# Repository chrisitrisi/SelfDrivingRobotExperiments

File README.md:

# SelfDrivingRobotExperiments

Wir verwenden ein vorgegebenes Modellfahrzeug als Basis. Wir entwickeln dafür eine eigene Platine, programmieren die Fahrzeugsoftware neu und erstellen ein eigenes 3D-Modell. Zusätzliche Entfernungssensoren sind eine Option.

| Bereich | Arbeitsstand |
| --- | --- |
| Hardware (Christopher) | [PCB](https://github.com/chrisitrisi/SelfDrivingRobotExperiments/tree/PCB/PCB) enthält KiCad-Projekte, darunter den Liniensensor. |
| Software | [Main_code](https://github.com/chrisitrisi/SelfDrivingRobotExperiments/tree/Main_code), [code](https://github.com/chrisitrisi/SelfDrivingRobotExperiments/tree/code) und [Test](https://github.com/chrisitrisi/SelfDrivingRobotExperiments/tree/Test) enthalten ESP-IDF-Sensorversuche. Den Ausgangsbranch pro Aufgabe im Issue angeben. |
| 3D-Design | [3D_Design](https://github.com/chrisitrisi/SelfDrivingRobotExperiments/tree/3D_Design/3D_Design-Modelling) enthält Fahrzeug- und Gehäusemodelle sowie Exporte. |
| Diplomarbeitsunterlagen | [Dokumentation](https://github.com/chrisitrisi/SelfDrivingRobotExperiments/tree/Dokumentation/Dokumentation) |

## Gemeinsam arbeiten

1. Erstellt ein [Issue](https://github.com/chrisitrisi/SelfDrivingRobotExperiments/issues/new) mit Ziel, Rolle, Ausgangsbranch und einem überprüfbaren Ergebnis. Bei Aufgaben für mehrere Bereiche beschreibt ihr die Teilaufgaben im selben Issue.
2. Lest die aktuelle [AGENTS.md](https://github.com/chrisitrisi/SelfDrivingRobotExperiments/blob/master/AGENTS.md), die [Schnittstellen](https://github.com/chrisitrisi/SelfDrivingRobotExperiments/blob/master/docs/schnittstellen.md) und die neuesten Issue-Kommentare. Die zentralen Dateien liegen auf `master`, auch wenn ihr gerade einen anderen Branch bearbeitet.
3. Erstellt euren Aufgabenbranch vom vereinbarten Fachbranch. Öffnet den Pull Request zurück in diesen Fachbranch und verlinkt das Issue. Änderungen an gemeinsamen Regeln und Schnittstellen gehen in einen eigenen Pull Request gegen `master`.
4. Haltet im Issue fest, was geprüft wurde, was offen ist und von welcher Rolle ihr eine Antwort braucht.

### KI-Fragen zwischen den Rollen

Die KIs der Rollen klären Fragen untereinander über Issues, ohne dass die Menschen dazwischen müssen: Eine KI stellt eine **KI-Frage** an eine Rolle (Labels `ki-frage` + `an:hardware`, `an:software` oder `an:3d`), die KI der Zielrolle antwortet im selben Issue. Fragen an die Hardware beantwortet eine GitHub Action mit Claude sofort automatisch (Rückfragen mit `@hw-ki`). Menschen werden nur über das Label [`braucht-mensch`](https://github.com/chrisitrisi/SelfDrivingRobotExperiments/issues?q=is%3Aopen+label%3Abraucht-mensch) gebraucht.

- Ablauf, Befehle, Antwortformat: [docs/ki-austausch.md](docs/ki-austausch.md)
- Wissen pro Rolle: [Hardware](docs/rollen/hardware.md) · [Software](docs/rollen/software.md) · [3D-Design](docs/rollen/3d-design.md)
- [Neue KI-Frage im Browser](https://github.com/chrisitrisi/SelfDrivingRobotExperiments/issues/new?template=ki-frage.yml)

### Projektstart im Terminal

Mit Python 3 und einer über `gh auth login` angemeldeten GitHub CLI könnt ihr im aktualisierten `master`-Checkout den Kontext zu einer Aufgabe anzeigen. Ersetzt 12 durch eine echte Issue-Nummer:

```sh
python tools/projektstart.py 12
```

Das Skript liest Regeln und Schnittstellen von GitHub sowie das Issue mit seinen Kommentaren. Es wechselt keinen Branch. In einem separaten Fachbranch-Checkout könnt ihr das Skript über seinen Pfad im `master`-Checkout starten.

### Prompt für Antigravity, Claude und ChatGPT

> Wir arbeiten in chrisitrisi/SelfDrivingRobotExperiments. Meine Rolle ist [Hardware, Software oder 3D-Design]. Bearbeite Issue #[Nummer]. Lies AGENTS.md, docs/schnittstellen.md und docs/ki-austausch.md vom aktuellen master sowie das Issue mit seinen Kommentaren. Prüfe zuerst den Posteingang meiner Rolle (Issues mit ki-frage und an:[rolle]) und beantworte offene Fragen. Brauchst du etwas von einer anderen Rolle, stelle eine KI-Frage statt mich zu fragen. Prüfe den dort genannten Fachbranch, bevor du Dateien bearbeitest. Arbeite auf einem Aufgabenbranch und adressiere den Pull Request an den Fachbranch. Teile Ergebnis, Prüfung und offene Fragen im Issue. Falls dir der Zugriff fehlt, benenne die fehlende Datei oder Aktion und liefere einen kopierbaren Entwurf.

Hinterlegt diesen Verweis in Browser-Projekten als Projektanweisung. Öffnet bei lokalen Tools den richtigen Repository-Ordner. Auf älteren Fachbranches können die zentralen Regeldateien fehlen. Gebt den Verweis dann beim Sitzungsstart mit. In Claude-Projekten mit synchronisierten Dateien vor der Arbeit den Stand von `master` aktualisieren und das Issue über ein GitHub-Werkzeug oder als Text bereitstellen.

**Zugriff testen:** Eine Person schreibt ein Prüfwort in ein Test-Issue. Die zweite KI liest es, antwortet im selben Issue und gibt den Kommentarlink zurück. Die dritte KI liest diese Antwort. Damit testet ihr Datei-, Issue- und Kommentarzugriff getrennt.

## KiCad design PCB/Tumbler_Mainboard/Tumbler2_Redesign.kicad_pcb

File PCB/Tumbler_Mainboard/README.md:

# Tumbler – Hauptplatine Rev. 2.5c (Schaltplan + Layout)

Das Projekt über **Tumbler2_Redesign.kicad_pro** in KiCad 10 öffnen. **Tumbler2_Redesign.pdf** zeigt die acht aktuellen Blätter (Rev. 2.5c, 28.11.2026).

- Blatt 2: USB-C-Freigabe, 2S-Ladegerät, VBUS-Erkennung. Blatt 7: Pack, Verpolschutz, Schalter, Fahrabschaltung und Spannungsregler.
- Blatt 5: ICM-42670-P, TB6612FNG, Motorencoder und externer Ultraschall. Blatt 8: I²C-Multiplexer TCA9548A und Lötpads J8–J15 für acht ToF-Sensoren (VL53L0X/GY-530).
- Blatt 7, Block 05: **2S/3S-Brücken** R87, R88, R89, R92 (0 Ω) mit R90/R91 und D14.
- README_Schaltplan.md: 2S/3S-Umbau mit Rechnung, Betriebsarten, Stecker, Adressen, Firmware und offene Hardwaretests. Stueckliste.csv nennt Wert, Bestückung, Footprint und Spezifikation. Pinbelegung.csv beschreibt den bestehenden Liniensensor.
## Rev. 2.5c · 28.11.2026

**3S ist die Standardbestückung.** R87, R88, R89, R92 und D14 (SMBJ8.5A, nur über R92 angeschlossen) bleiben frei. Die KiCad-Variante `2S` bestückt diese vier 0-Ω-Brücken und D14. R90 und R91 gehören in beide Varianten. Akku und USB vor jeder Umrüstung trennen. 3S extern laden. Die 2S-Ladefunktion benötigt OFF, einen passenden Pack-NTC und eine geeignete USB-C-Quelle.

Die [Fertigungsanleitung](Fertigung/README.md) nennt die zusammengehörigen Dateien für beide Varianten. Das Hauptboard benötigt für die ausgewählten Bauteile JLC Standard PCBA. Der Liniensensor bleibt ein eigener Economic-Auftrag.

C69 sitzt weiter von der H4-Stütze entfernt. Der NTC-Anschluss an TP8 wurde neu geführt und die benachbarte Kupferengstelle beseitigt. Die zwei Massevias nahe D14.2 liegen außerhalb der Lötfläche. Für die Passprobe mit Akku und Kabelbaum steht im Mechanikordner eine bestückte 3S-Baugruppe zur Verfügung.

### Frühere Revisionen

- **Rev. 2.5b (28.11.2026)**
  - BQ25886-Leistungsschleife kompakt: C36/C37 (SYS) direkt an Pin 15/16, L3 ~2 mm vom SW-Pin, C40 (BAT) nah, C30 (BTST) und C31 (REGN) direkt am IC, R49/R50 jetzt 0402 unter U12. C72 (1 µF) direkt an U9-Eingang.
  - Nicht lieferbare Teile ersetzt: **U2 AP63201WU-7** (einstellbar) mit Teiler **R93 47k / R94 15k** → 3,31 V; **U14 TLV3011** (Open-Drain) → **R55 jetzt Pull-up nach USB_3V3**; **L3 XEL4030-102MEC** (gleicher Footprint); C17 330 µF/25 V SMD 10×10; D2 rote Basic-LED; WS2812B-2020-V6.
  - Kosten: Kondensatoren auf Basic-Teile umgestellt, C1/C3/C6/C7/C25/C26/C65 auf eine Teilenummer (22 µF/25 V 1210). Alle SMD-Teile mit LCSC-Nummer, R5/R6 hatten vorher die Nummer eines 4,7-k-Widerstands.
  - J8–J15 neuer Footprint `Tumbler2:TOF_Wire_1x04_P2.54mm` (enger Courtyard), DRC-Regeldatei `Tumbler2_Redesign.kicad_dru` für J4 und die U3-Antenne.
  - Bestückungstexte kleiner Bauteile auf der Oberseite ausgeblendet (lagen auf Pads), dafür `Fertigung/Bestueckungsplan_oben/unten.pdf`.
  - KiCad 10.0.7: **ERC 0, DRC 0 Fehler, 0 offene Verbindungen, 0 Paritätsfehler.** Damals 69 Warnungen, darunter eine Kupferengstelle und Hinweise (Siebdruck an Footprint-Grafiken/Rand, geänderte Testpunkt-Footprints, 5 Leiterbahnenden auf Padmitte).
  - Die damalige Economic-Empfehlung wurde in Rev. 2.5c nach Abgleich mit dem JLC-Katalog korrigiert.
- **Rev. 2.5a (26.11.2026): Korrekturen vor der JLC-Bestellung.**
  - J12/J13 (ToF CH4/CH5) um 2,54 mm nach rechts: Die Lötstellen J12.1/J13.1 lagen 4,7/4,5 mm neben H4 und damit auf der Gehäusestütze (Ø 11 mm). Jetzt ≥ 7,0 mm Abstand. R79/R81 (Pull-ups) dafür auf freie Plätze der Unterseite versetzt. Mechanik/Gehauese_Bezugspunkte.csv angepasst.
  - Keine Vias mehr in Lötpads von Signalen (vorher R73.2, J6.4, U3 Pin 2 und 39, GND an J6.2/J7.2/D14.2). Nur die Wärme-Vias in den Thermalpads von U3 (Pin 41) und U12 (Pin 25) bleiben bewusst.
  - Alle Texte auf der Unterseite gespiegelt (vorher 78 spiegelverkehrte Bestückungstexte).
  - J1-Wert „Akku 2S/3S“. Damals war 2S die Auslieferung: R87/R88/R89/R92 = 0 Ω bestückt.
  - KiCad 10.0.7: ERC 0, 0 offene Verbindungen, 0 Paritätsfehler. Bekannt/akzeptiert: 8 Pad-zu-NPTH-Abstände an J4 (Hersteller-Footprint, im JLC-DFM-Check ansehen), 6 Courtyard-Überlappungen ohne Kupferkonflikt.
  - **Bei JLC bestellen mit Innenlagen 1 oz** (Standard ist 0,5 oz): Motor- und Akkuleitungen laufen teilweise auf In2.Cu.
  - (Die damals offenen Punkte BQ25886-Schleife und U9-Eingangskondensator sind in Rev. 2.5b erledigt.)
- **Rev. 2.5 (19.11.2026): Akku 2S oder 3S.** Vier 0-Ω-Brücken auf der Unterseite (Kasten „2S | 3S“ unter U16): **alle bestückt = 2S** (Auslieferung, alte JST-XH-Akkus unverändert), **alle entfernt = 3S – R87 zuerst!**
  - R87 trennt den Lader (BQ25886 BAT, abs. max. 12 V) bei 3S ab (neues Netz CHG_BAT).
  - R88/R91: LTC4365-OV 8,75 V (2S) bzw. 13,52 V (3S). UV bleibt 5,50 V. In 2S-Stellung sperrt der LTC einen falsch gesteckten 3S-Akku.
  - R89/R90: Fahrfreigabe TPS3700 6,42/6,00 V (2S) bzw. 9,66/9,03 V (3S).
  - D1 jetzt SMBJ13A, zusätzlich D14 SMBJ8.5A über R92 (nur 2S). C17 220 µF/25 V, C63 100 nF/25 V.
  - Leistungsbahnen BAT_RAW, PROT_SRC, BAT_FUSED, PACK_SAFE, VBAT_SW überwiegend auf 0,6–0,65 mm verbreitert, wo der Abstand es zulässt (Motornetze M1/M2 meist noch 0,4 mm).
  - DRC-Korrekturen aus der Testkopie übernommen (SDA5-Verbindung, J4-VBUS-Brücke, ENCB_B aus der Antennensperrfläche, doppelte Via, Netznamen/Felder), Abstandsregel 0,125 mm. ERC-Kosmetik in peripherals (Encoder-Stummel) behoben.
  - Prüfung mit kicad-cli: **ERC 0, DRC 0 offene Verbindungen, 0 Abstands-, 0 Paritätsfehler.** Verbleibend: 8 × Lochabstand am USB-C-Footprint J4 (Herstellerfootprint, akzeptiert) und 7 bekannte Courtyard-Überlappungen (J12/J13, H4–J12/J13, U9/J12, C41/U13, U11/C31, U3/J6).
  - Firmware: `Hinweise_Software_Rev2.5.md`, Issue-Entwurf `Issue_Software_2S3S_Akku.md`.
- Rev. 2.4b (18.11.2026): Akkustecker J1 von Molex Micro-Fit 4-polig auf JST XH 2-polig (B2B-XH-A) geändert, damit die vorhandenen 2S-Akkus direkt passen. Onboard-Laden ist ohne NTC gesperrt, die Akkus werden extern geladen.
- Rev. 2.4 (12.11.2026): 8 ToF-Ports J8–J15 (J12-Leiste ersetzt durch Lötpads J12–J15, Pull-ups R79–R86, Abblockung C69–C71 auf der Unterseite), Multiplexer-RESET MUX_RSTn an GPIO37, Schaltplanblätter übersichtlich neu gezeichnet (GND nach unten, 3,3 V/5 V nach oben). Firmware-Hinweise damals: Hinweise_Software_Rev2.4.md (jetzt im Backup-Ordner) und GitHub-Issue.
- Rev. 2.3 (11.11.2026): ToF-Vorgaben der Software umgesetzt – TCA9548A (8 Kanäle), J8–J11 als Lötpads für GY-530-Kabel (VIN = +5 V, GND, SCL, SDA), J12 für CH4–CH7, alle I²C-Pull-ups 2,2 kΩ an +3,3 V. 
- Rev. 2.2 (11.11.2026): Akkuspannungsmessung R77/R78/C67 an GPIO3, J3 mit TXD0/RXD0/EN/IO0, README um Ladestrom-Begründung und Bremstest ergänzt.
- Pruefung/ enthält den aktuellen ERC, die exportierte Netzliste und die Ergebnisse der Pinprüfungen. TumblerBasis.kicad_sym bindet die übernommenen KiCad-Basissymbole ans Projekt; Quellen/Lizenz siehe LICENSE_KiCad_Bibliotheken.txt.

**Layout Rev. 2.4/2.5:** 4 Lagen – F.Cu Signal, In1.Cu durchgehende GND-Fläche, In2.Cu Signal, B.Cu Signal (GND-Flächen auf allen Lagen, beim Öffnen mit **B** füllen). Alle Bauteile neu platziert und vollständig geroutet. Stand Rev. 2.5 mit KiCad-DRC (kicad-cli, Flächen neu gefüllt) geprüft, siehe oben.
- ESP32-S3 an der rechten Kante, Antenne ragt über die Platine hinaus; Kupfer-Sperrflächen neben der Antenne auf allen Lagen, unter dem Antennenteil des Moduls kein Kupfer auf F.Cu.
- Vorne (Unterkante): 8 RGB-LEDs D6–D13, Liniensensor-Stecker J2, ToF-Lötpads J8 (vorne), J12/J13 daneben. Rechte Roboterseite (linke Bildkante): J9–J11, USB-C J4. J14 an der Hinterkante, J15 hinten links neben J1.
- Platzierungsuebersicht.png und Gehauese_Bezugspunkte.csv (Ursprung links unten, Y nach oben) in Mechanik/ entsprechen diesem Stand.
- Vor der Fertigung in KiCad: Flächen füllen, DRC laufen lassen, Bestückungsdruck prüfen. Hinweis: Bereich J12/U13/H4 hat knappe Courtyards (Kupfer frei).

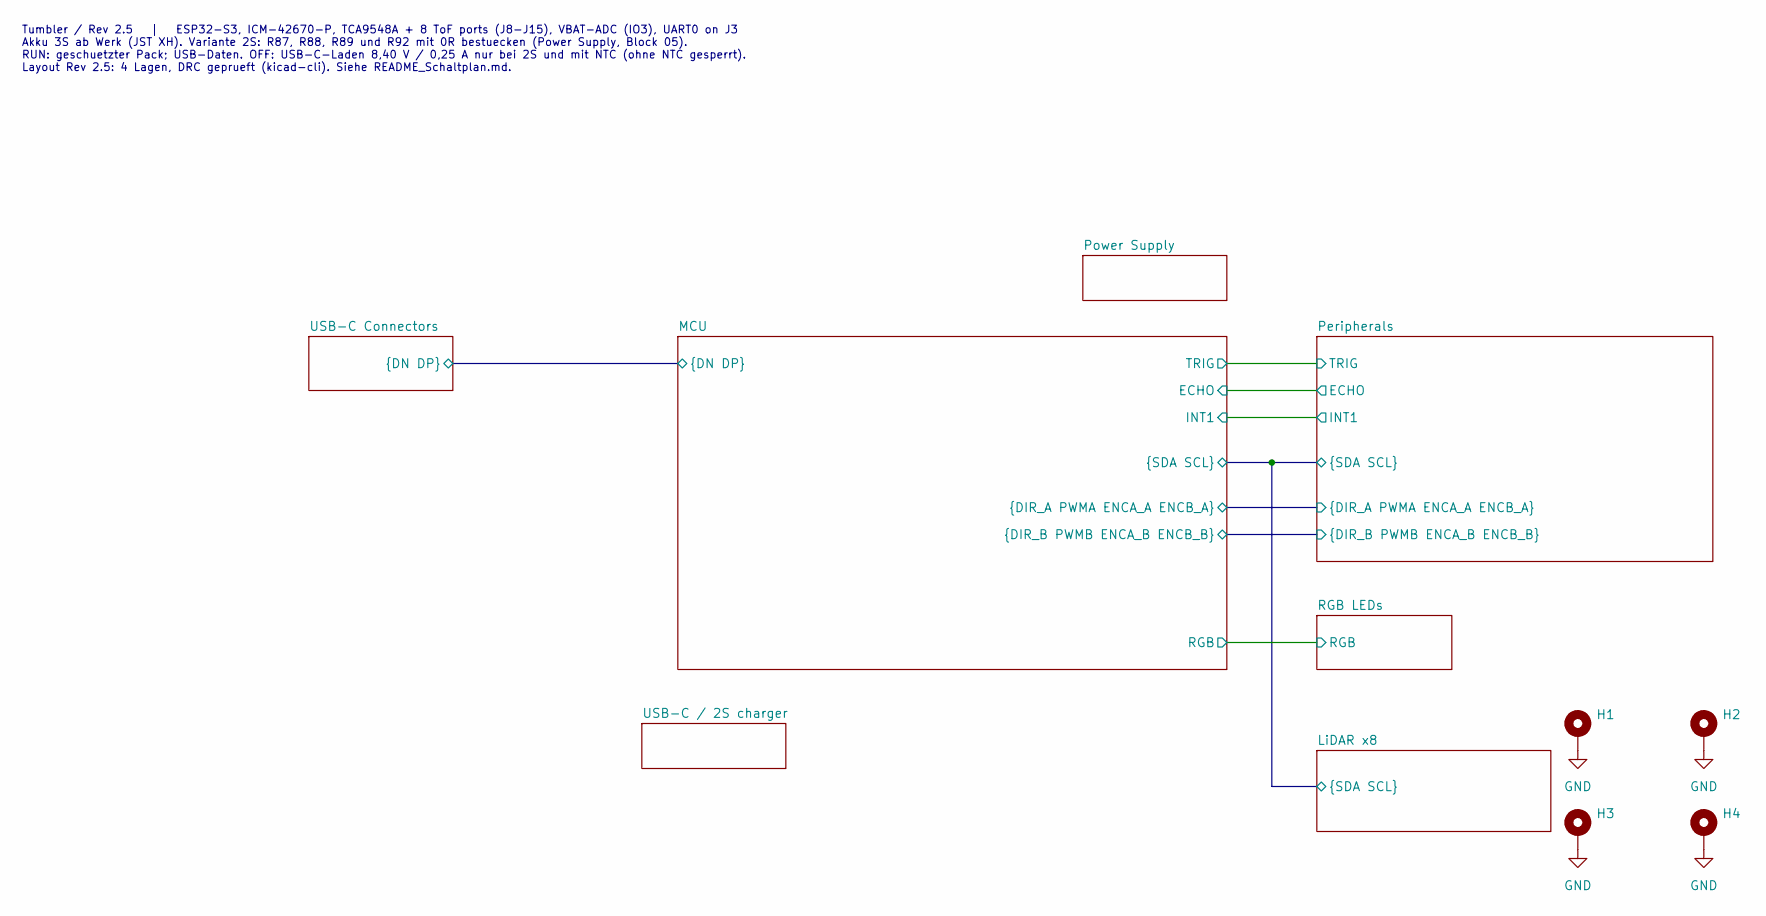
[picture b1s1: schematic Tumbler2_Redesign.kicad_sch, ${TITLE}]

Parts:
H1, H2, H3, H4: MountingHole_Pad; MountingHole_3mm_Pad_Via

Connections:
GND: H1.1, H2.1, H3.1, H4.1; also elsewhere on the board

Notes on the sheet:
Tumbler / Rev 2.5 | ESP32-S3, ICM-42670-P, TCA9548A + 8 ToF ports (J8-J15), VBAT-ADC (IO3), UART0 on J3 Akku 3S ab Werk (JST XH). Variante 2S: R87, R88, R89 und R92 mit 0R bestuecken (Power Supply, Block 05). RUN: geschuetzter Pack; USB-Daten. OFF: USB-C-Laden 8,40 V / 0,25 A nur bei 2S und mit NTC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

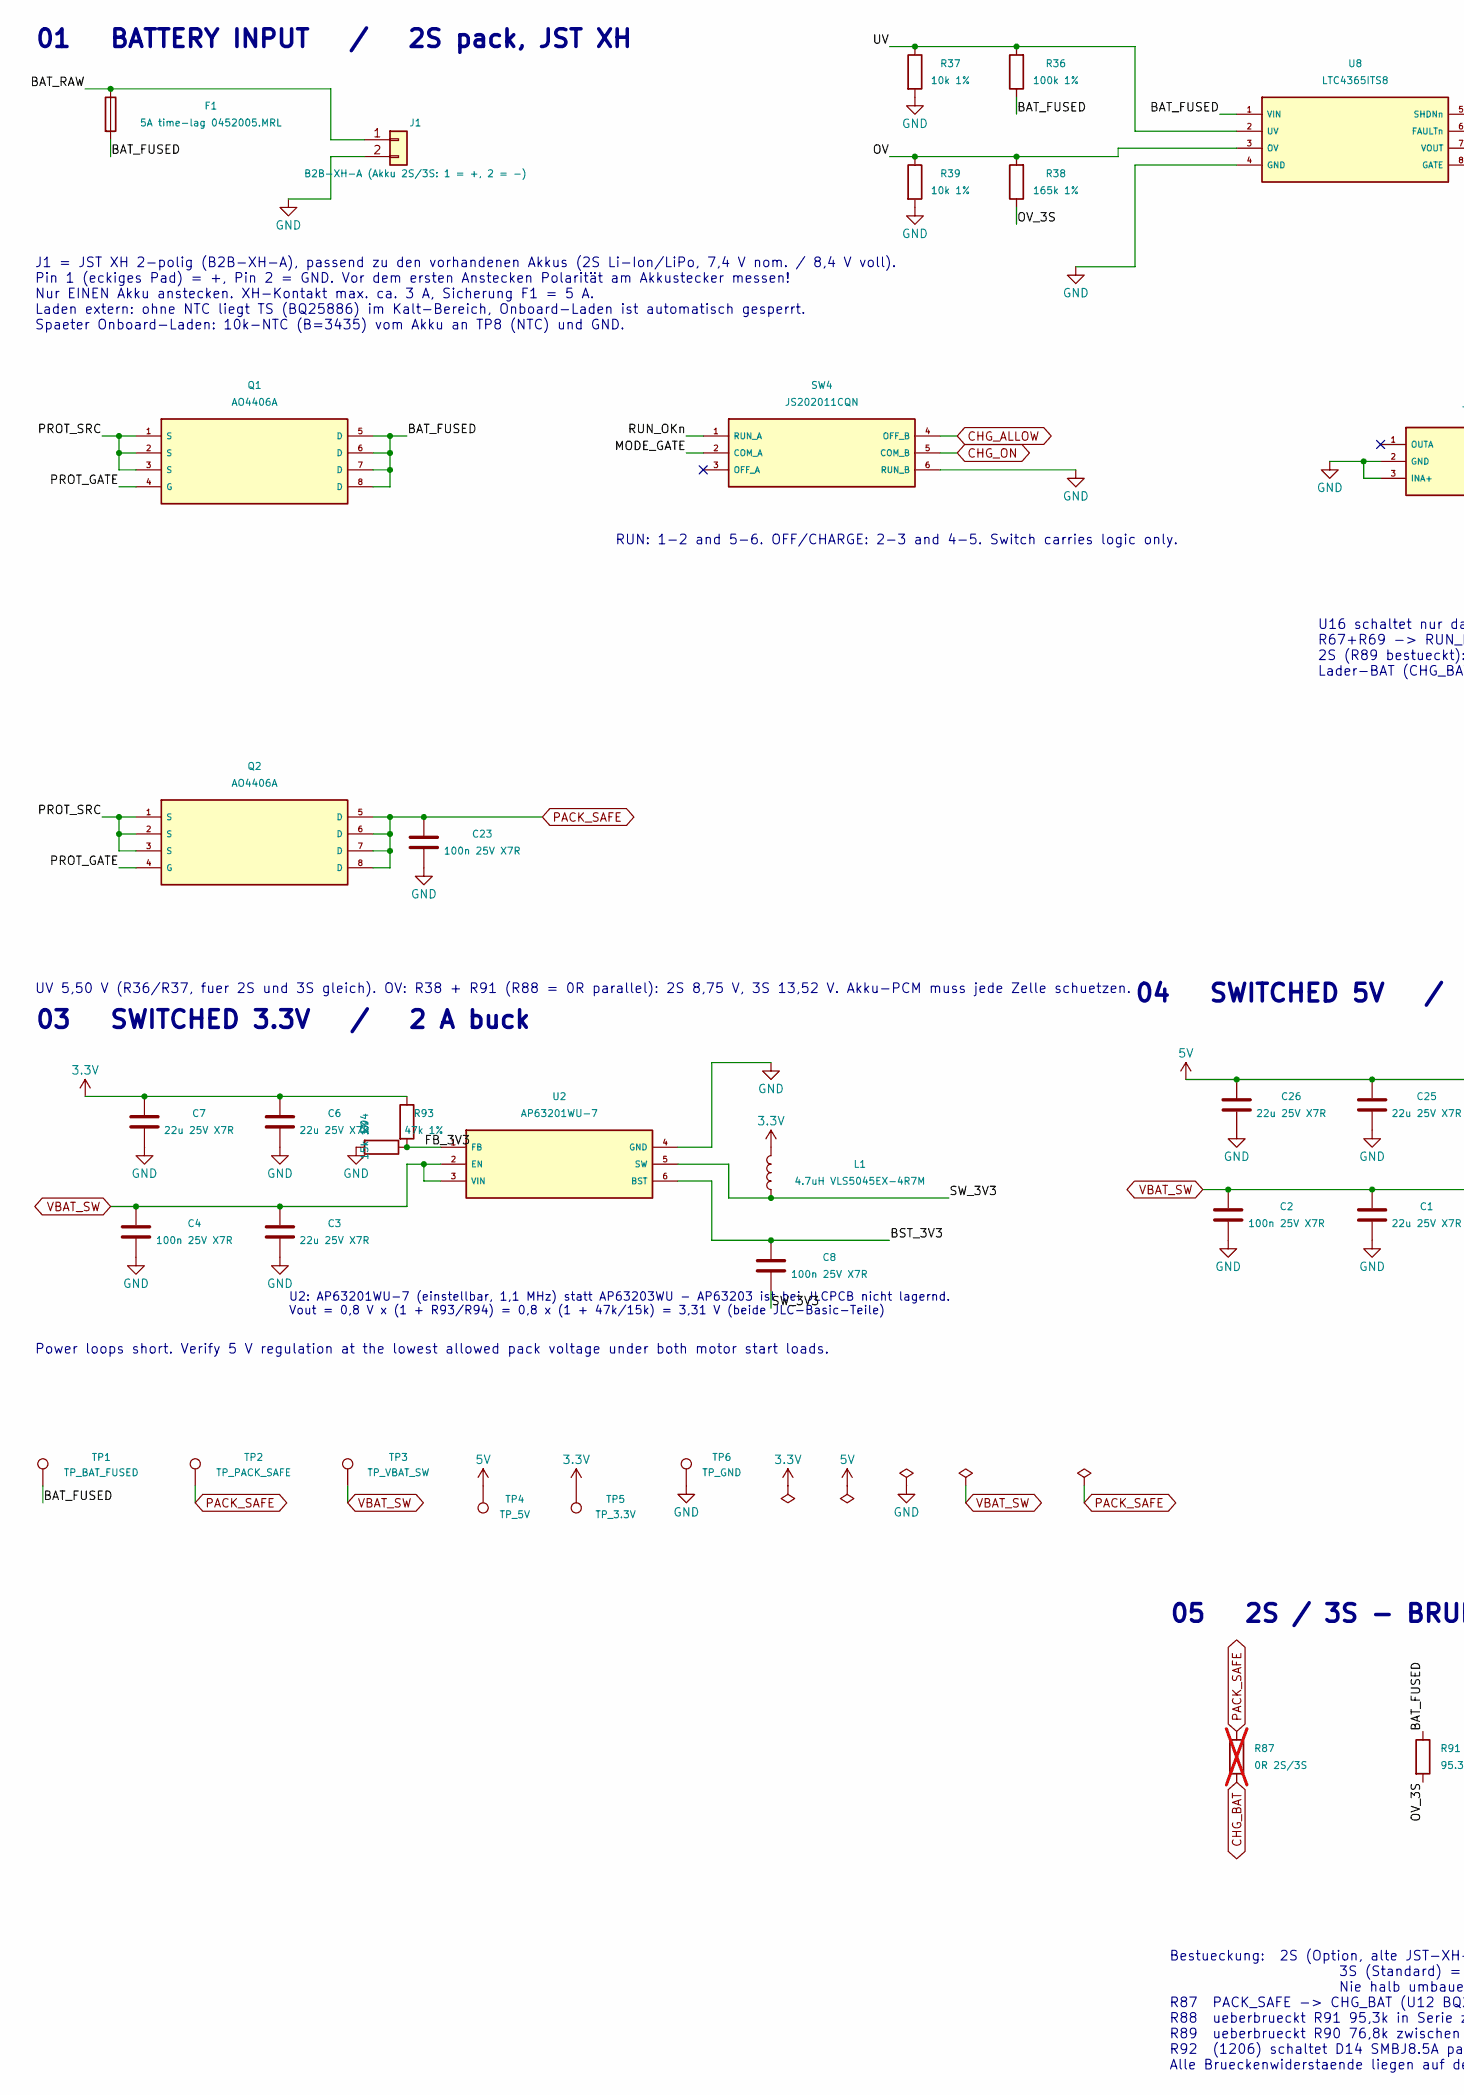
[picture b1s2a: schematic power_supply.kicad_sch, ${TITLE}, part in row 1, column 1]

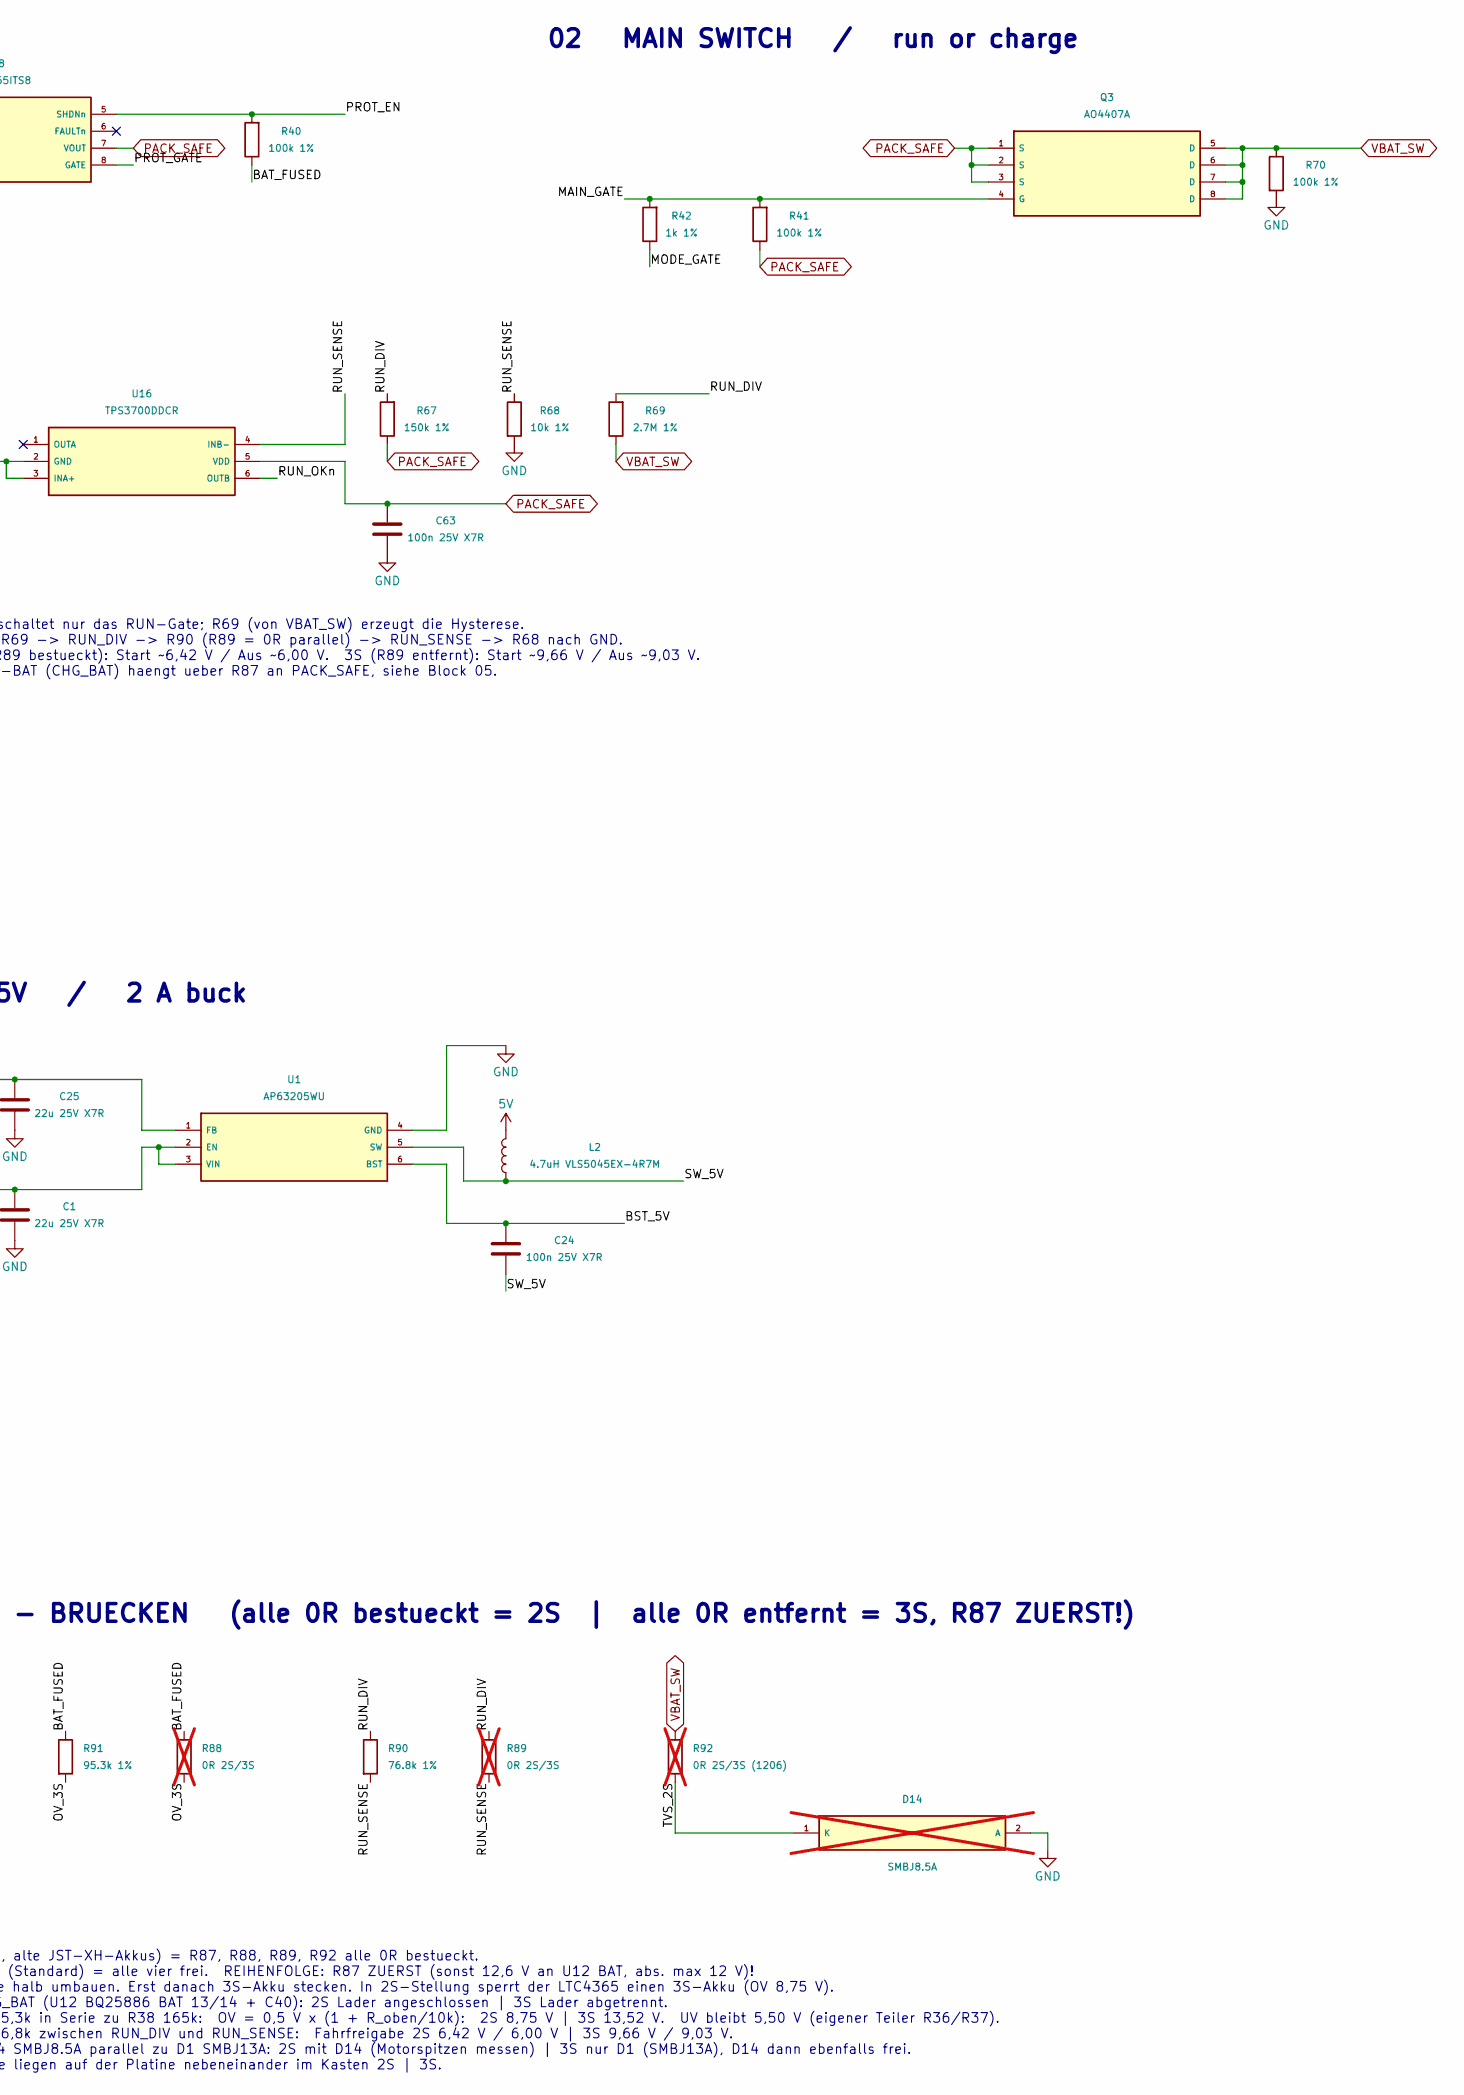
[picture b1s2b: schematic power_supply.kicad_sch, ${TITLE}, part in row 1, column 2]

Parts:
C1, C3, C6, C7, C25, C26: 22u 25V X7R; C_1210_3225Metric; LCSC PN C309062
C2, C4, C8, C23, C24, C63: 100n 25V X7R; C_0603_1608Metric; LCSC PN C14663
D14: SMBJ8.5A; D_SMB; LCSC PN C353329; not fitted
F1: 5A time-lag 0452005.MRL; Fuse_Littelfuse-NANO2-451_453; LCSC PN C66503
J1: B2B-XH-A (Akku 2S/3S: 1 = +, 2 = -); JST_XH_B2B-XH-A_1x02_P2.50mm_Vertical; LCSC PN C158012
L1, L2: 4.7uH VLS5045EX-4R7M; VLS5045EX-4R7M; LCSC PN C307876
Q1, Q2: AO4406A; SOIC-8_3.9x4.9mm_P1.27mm; LCSC PN C5155213
Q3: AO4407A; SOIC-8_3.9x4.9mm_P1.27mm; LCSC PN C2841482
R36, R40, R41, R70: 100k 1%; R_0603_1608Metric; LCSC PN C25803
R37, R39, R68: 10k 1%; R_0603_1608Metric; LCSC PN C25804
R38: 165k 1%; R_0603_1608Metric; LCSC PN C22816
R42: 1k 1%; R_0603_1608Metric; LCSC PN C21190
R67: 150k 1%; R_0603_1608Metric; LCSC PN C22807
R69: 2.7M 1%; R_0603_1608Metric; LCSC PN C26095
R87, R88, R89: 0R 2S/3S; R_0603_1608Metric; LCSC PN C21189; not fitted
R90: 76.8k 1%; R_0603_1608Metric; LCSC PN C165743
R91: 95.3k 1%; R_0603_1608Metric; LCSC PN C23267
R92: 0R 2S/3S (1206); R_1206_3216Metric; LCSC PN C17888; not fitted
R93: 47k 1%; R_0603_1608Metric; LCSC PN C25819
R94: 15k 1%; R_0603_1608Metric; LCSC PN C22809
SW4: JS202011CQN; SW_CK_JS202011CQN_DPDT_Straight; LCSC PN C221663
TP1: TP_BAT_FUSED; TestPoint_Pad_D1.0mm
TP2: TP_PACK_SAFE; TestPoint_Pad_D1.0mm
TP3: TP_VBAT_SW; TestPoint_Pad_D1.0mm
TP4: TP_5V; TestPoint_Pad_D1.0mm
TP5: TP_3.3V; TestPoint_Pad_D1.0mm
TP6: TP_GND; TestPoint_Pad_D1.0mm
U1: AP63205WU; TSOT-23-6; LCSC PN C2071056
U2: AP63201WU-7; TSOT-23-6; LCSC PN C2071044
U8: LTC4365ITS8; TSOT-23-8; LCSC PN C688321
U16: TPS3700DDCR; TSOT-23-6; LCSC PN C33002

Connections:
3.3V: C6.1, C7.1, L1.2, R93.1, TP5.1; also elsewhere on the board
5V: C25.1, C26.1, L2.2, TP4.1, U1.1 (FB); also elsewhere on the board
/Power Supply/BAT_FUSED: F1.2, Q1.5 (D), Q1.6 (D), Q1.7 (D), Q1.8 (D), R36.1, R40.1, R88.1, R91.1, TP1.1, U8.1 (VIN)
/Power Supply/BAT_RAW: F1.1, J1.1
/Power Supply/BST_3V3: C8.1, U2.6 (BST)
/Power Supply/BST_5V: C24.1, U1.6 (BST)
/Power Supply/FB_3V3: R93.2, R94.1, U2.1 (FB)
/Power Supply/MAIN_GATE: Q3.4 (G), R41.2, R42.2
/Power Supply/MODE_GATE: R42.1, SW4.2 (COM_A)
/Power Supply/OV: R38.2, R39.1, U8.3 (OV)
/Power Supply/OV_3S: R38.1, R88.2, R91.2
/Power Supply/PROT_EN: R40.2, U8.5 (SHDNn)
/Power Supply/PROT_GATE: Q1.4 (G), Q2.4 (G), U8.8 (GATE)
/Power Supply/PROT_SRC: Q1.1 (S), Q1.2 (S), Q1.3 (S), Q2.1 (S), Q2.2 (S), Q2.3 (S)
/Power Supply/RUN_DIV: R67.2, R69.2, R89.1, R90.1
/Power Supply/RUN_OKn: SW4.1 (RUN_A), U16.6 (OUTB)
/Power Supply/RUN_SENSE: R68.1, R89.2, R90.2, U16.4 (INB-)
/Power Supply/SW_3V3: C8.2, L1.1, U2.5 (SW)
/Power Supply/SW_5V: C24.2, L2.1, U1.5 (SW)
/Power Supply/TVS_2S: D14.1 (K), R92.2
/Power Supply/UV: R36.2, R37.1, U8.2 (UV)
CHG_ALLOW: SW4.4 (OFF_B); also elsewhere on the board
CHG_BAT: R87.2; also elsewhere on the board
CHG_ON: SW4.5 (COM_B); also elsewhere on the board
GND: C1.2, C2.2, C3.2, C4.2, C6.2, C7.2, C23.2, C25.2, C26.2, C63.2, D14.2 (A), J1.2, R37.2, R39.2, R68.2, R70.2, R94.2, SW4.6 (RUN_B), TP6.1, U1.4 (GND), U2.4 (GND), U8.4 (GND), U16.2 (GND), U16.3 (INA+); also elsewhere on the board
PACK_SAFE: C23.1, C63.1, Q2.5 (D), Q2.6 (D), Q2.7 (D), Q2.8 (D), Q3.1 (S), Q3.2 (S), Q3.3 (S), R41.1, R67.1, R87.1, TP2.1, U8.7 (VOUT), U16.5 (VDD)
VBAT_SW: C1.1, C2.1, C3.1, C4.1, Q3.5 (D), Q3.6 (D), Q3.7 (D), Q3.8 (D), R69.1, R70.1, R92.1, TP3.1, U1.2 (EN), U1.3 (VIN), U2.2 (EN), U2.3 (VIN); also elsewhere on the board

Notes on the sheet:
Bestueckung: 2S (Option, alte JST-XH-Akkus) = R87, R88, R89, R92 alle 0R bestueckt. 3S (Standard) = alle vier frei. REIHENFOLGE: R87 ZUERST (sonst 12,6 V an U12 BAT, abs. max 12 V)! Nie halb umbauen. Erst danach 3S-Akku stecken. In 2S-Stellung sperrt der LTC4365 einen 3S-Akku (OV 8,75 V). R87 PACK_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
01 BATTERY INPUT / 2S pack, JST XH
J1 = JST XH 2-polig (B2B-XH-A), passend zu den vorhandenen Akkus (2S Li-Ion/LiPo, 7,4 V nom. / 8,4 V voll). Pin 1 (eckiges Pad) = +, Pin 2 = GND. Vor dem ersten Anstecken Polarität am Akkustecker messen! Nur EINEN Akku anstecken. XH-Kontakt max. ca. 3 A, Sicherung F1 = 5 A. Laden extern: ohne NTC l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
U16 schaltet nur das RUN-Gate; R69 (von VBAT_SW) erzeugt die Hysterese. R67+R69 -> RUN_DIV -> R90 (R89 = 0R parallel) -> RUN_SENSE -> R68 nach GND. 2S (R89 bestueckt): Start ~6,42 V / Aus ~6,00 V. 3S (R89 entfernt): Start ~9,66 V / Aus ~9,03 V. Lader-BAT (CHG_BAT) haengt ueber R87 an PACK_SAFE, sie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
UV 5,50 V (R36/R37, fuer 2S und 3S gleich). OV: R38 + R91 (R88 = 0R parallel): 2S 8,75 V, 3S 13,52 V. Akku-PCM muss jede Zelle schuetzen.
04 SWITCHED 5V / 2 A buck
03 SWITCHED 3.3V / 2 A buck
Power loops short. Verify 5 V regulation at the lowest allowed pack voltage under both motor start loads.
05 2S / 3S - BRUECKEN (alle 0R bestueckt = 2S | alle 0R entfernt = 3S, R87 ZUERST!)
RUN: 1-2 and 5-6. OFF/CHARGE: 2-3 and 4-5. Switch carries logic only.
02 MAIN SWITCH / run or charge
U2: AP63201WU-7 (einstellbar, 1,1 MHz) statt AP63203WU - AP63203 ist bei JLCPCB nicht lagernd. Vout = 0,8 V x (1 + R93/R94) = 0,8 x (1 + 47k/15k) = 3,31 V (beide JLC-Basic-Teile)

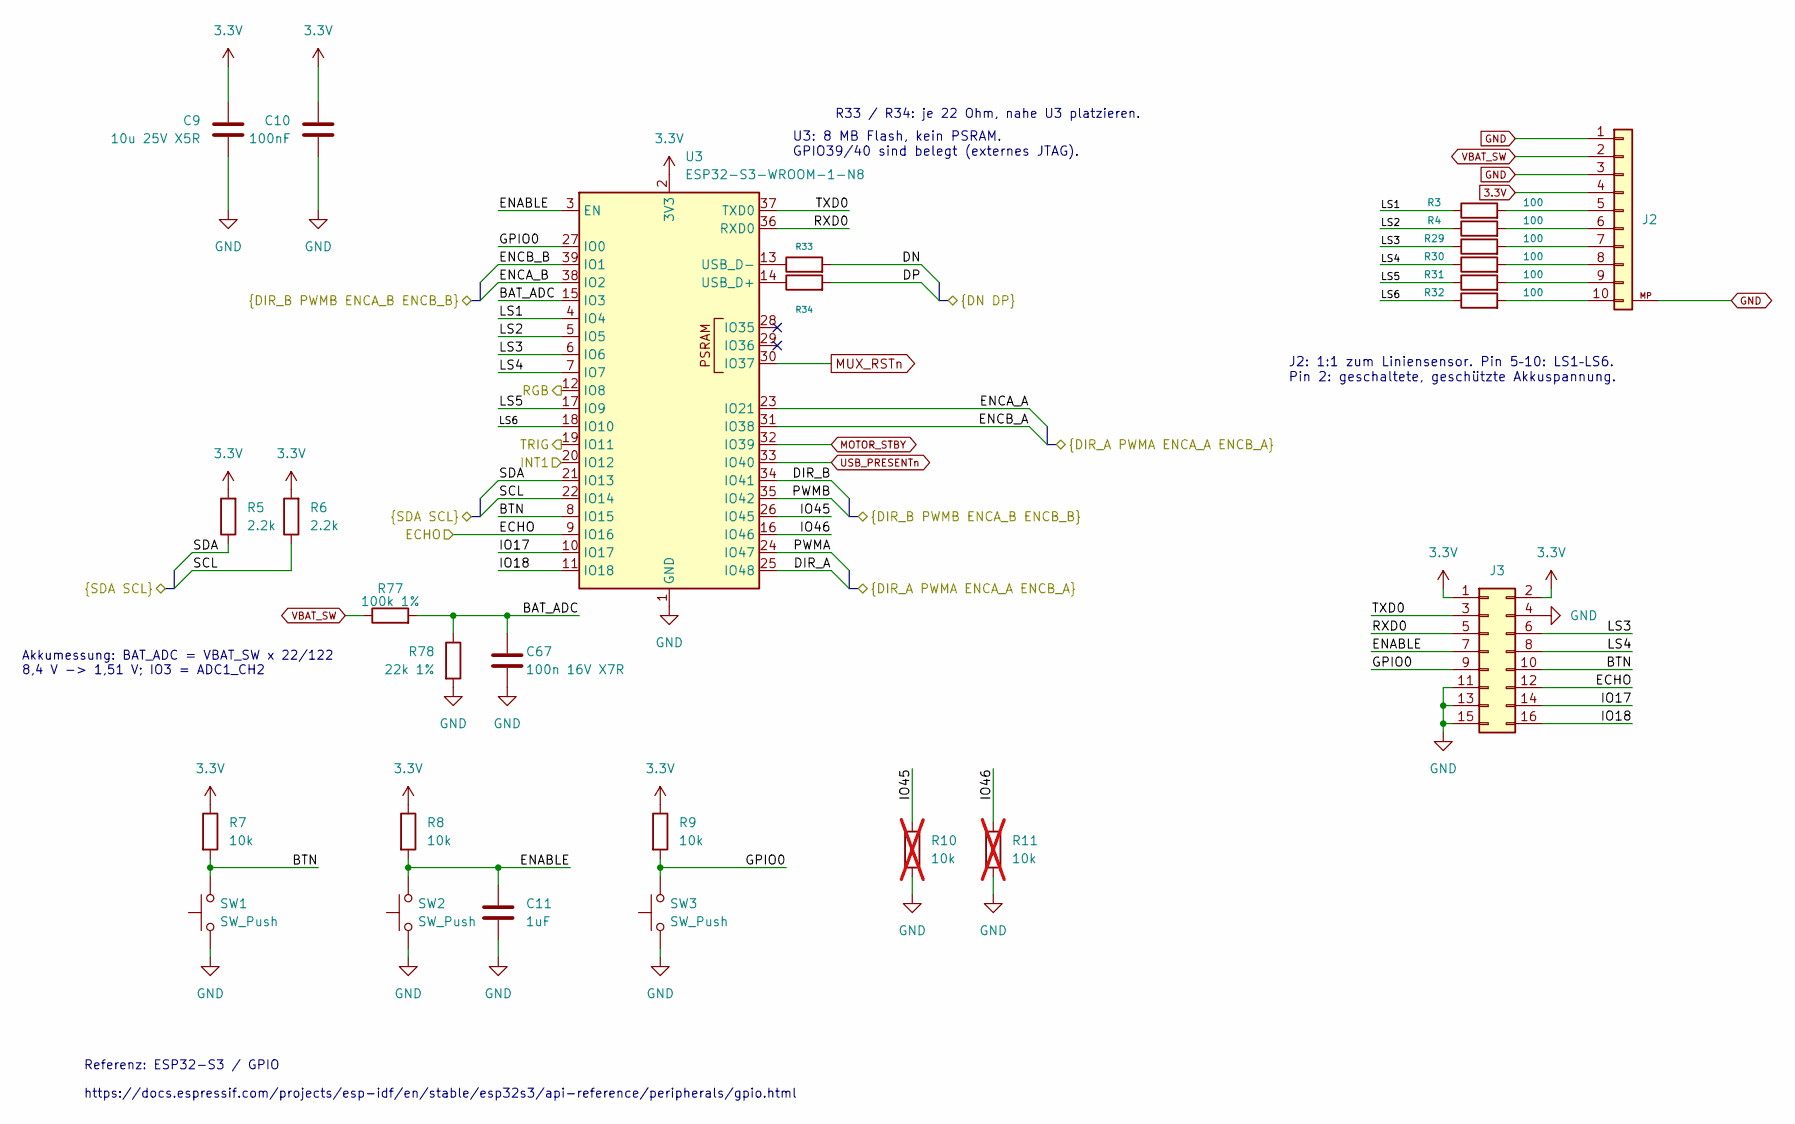
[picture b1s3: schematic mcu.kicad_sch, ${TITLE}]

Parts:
C9: 10u 25V X5R; C_0603_1608Metric; LCSC PN C96446
C10: 100nF; C_0603_1608Metric; LCSC PN C14663
C11: 1uF; C_0603_1608Metric; LCSC PN C59782
C67: 100n 16V X7R; C_0603_1608Metric; LCSC PN C14663
J2: JST_GH_BM10B-GHS-TBT; JST_GH_BM10B-GHS-TBT_1x10-1MP_P1.25mm_Vertical; LCSC PN C495732
J3: Conn_02x08_Odd_Even; PinHeader_2x08_P2.54mm_Vertical; LCSC PN C68234
R3, R4, R29, R30, R31, R32: 100; R_0603_1608Metric; LCSC PN C22775
R5, R6: 2.2k; R_0603_1608Metric; LCSC PN C4190
R7, R8, R9: 10k; R_0603_1608Metric; LCSC PN C25804
R10, R11: 10k; R_0603_1608Metric; LCSC PN C25804; not fitted
R33, R34: 22; R_0603_1608Metric; LCSC PN C23345
R77: 100k 1%; R_0603_1608Metric; LCSC PN C25803
R78: 22k 1%; R_0603_1608Metric; LCSC PN C31850
SW1, SW2, SW3: SW_Push; SW_TS-1088-AR02016; LCSC PN C720477
U3: ESP32-S3-WROOM-1-N8; ESP32-S3-WROOM-1; LCSC PN C2913198

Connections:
3.3V: C9.1, C10.1, J2.4, J3.1, J3.2, R5.2, R6.2, R7.1, R8.1, R9.1, U3.2 (3V3); also elsewhere on the board
/LiDAR x8/SCL: R6.1, U3.22 (IO14); also elsewhere on the board
/LiDAR x8/SDA: R5.1, U3.21 (IO13); also elsewhere on the board
/MCU/BAT_ADC: C67.1, R77.2, R78.1, U3.15 (IO3)
/MCU/BTN: J3.10, R7.2, SW1.2, U3.8 (IO15)
/MCU/DIR_A: U3.25 (IO48); also elsewhere on the board
/MCU/DIR_B: U3.34 (IO41); also elsewhere on the board
/MCU/DN: R33.2; also elsewhere on the board
/MCU/DP: R34.2; also elsewhere on the board
/MCU/ECHO: J3.12, U3.9 (IO16); also elsewhere on the board
/MCU/ENABLE: C11.1, J3.7, R8.2, SW2.2, U3.3 (EN)
/MCU/ENCA_A: U3.23 (IO21); also elsewhere on the board
/MCU/ENCA_B: U3.38 (IO2); also elsewhere on the board
/MCU/ENCB_A: U3.31 (IO38); also elsewhere on the board
/MCU/ENCB_B: U3.39 (IO1); also elsewhere on the board
/MCU/GPIO0: J3.9, R9.2, SW3.2, U3.27 (IO0)
/MCU/INT1: U3.20 (IO12); also elsewhere on the board
/MCU/IO17: J3.14, U3.10 (IO17)
/MCU/IO18: J3.16, U3.11 (IO18)
/MCU/IO45: R10.1, U3.26 (IO45)
/MCU/IO46: R11.1, U3.16 (IO46)
/MCU/LS1: R3.1, U3.4 (IO4)
/MCU/LS2: R4.1, U3.5 (IO5)
/MCU/LS3: J3.6, R29.1, U3.6 (IO6)
/MCU/LS4: J3.8, R30.1, U3.7 (IO7)
/MCU/LS5: R31.1, U3.17 (IO9)
/MCU/LS6: R32.1, U3.18 (IO10)
/MCU/PWMA: U3.24 (IO47); also elsewhere on the board
/MCU/PWMB: U3.35 (IO42); also elsewhere on the board
/MCU/RXD0: J3.5, U3.36 (RXD0)
/MCU/TRIG: U3.19 (IO11); also elsewhere on the board
/MCU/TXD0: J3.3, U3.37 (TXD0)
/RGB LEDs/RGB: U3.12 (IO8); also elsewhere on the board
GND: C9.2, C10.2, C11.2, C67.2, J2.1, J2.3, J2.MP, J3.4, J3.11, J3.13, J3.15, R10.2, R11.2, R78.2, SW1.1, SW2.1, SW3.1, U3.1 (GND), U3.40 (GND), U3.41 (GND); also elsewhere on the board
MOTOR_STBY: U3.32 (IO39); also elsewhere on the board
MUX_RSTn: U3.30 (IO37); also elsewhere on the board
unnamed: J2.5, R3.2
unnamed: J2.6, R4.2
unnamed: J2.7, R29.2
unnamed: J2.8, R30.2
unnamed: J2.9, R31.2
unnamed: J2.10, R32.2
unnamed: R34.1, U3.14 (USB_D+)
unnamed: R33.1, U3.13 (USB_D-)
USB_PRESENTn: U3.33 (IO40); also elsewhere on the board
VBAT_SW: J2.2, R77.1; also elsewhere on the board

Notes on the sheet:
R33 / R34: je 22 Ohm, nahe U3 platzieren.
U3: 8 MB Flash, kein PSRAM. GPIO39/40 sind belegt (externes JTAG).
Akkumessung: BAT_ADC = VBAT_SW x 22/122 8,4 V -> 1,51 V; IO3 = ADC1_CH2
J2: 1:1 zum Liniensensor. Pin 5–10: LS1–LS6. Pin 2: geschaltete, geschützte Akkuspannung.
Referenz: ESP32-S3 / GPIO
https://docs.espressif.com/projects/esp-idf/en/stable/esp32s3/api-reference/peripherals/gpio.html
